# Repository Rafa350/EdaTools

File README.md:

# EdaTools

Tools and utilities for PCB design.
!!!Very early version. Runs ok for my works.

## EdaImport
* Convert EAGLE v7 BRD file to EdaTools board file (.XBRD)
* Convert EAGLE v7 LBR file to EdaTools library file (.XLIB)
* Convert KiCad pcb file to EdaTools board file (.XBRD)

## EdaExport
* Convert EdaTools board file (.XBRD) to EAGLE or KiCAD
* Convert EdaTools library file (.XLIB) to KiCAD footprint library

## EdaExtractor.
* Extract information from board (BOM, Centroids, etc)

## EdaPanelizer.
* Merge any number of boards to create a single board panel.

## EdaCAMTool.
* Create production files from CAM project file (.XCAM).
* Generate gerber X3 image files.
* Generate gerber X3 drill and route files.
* Generate IPC-D356 file.
* Generate IPC-2581C file.
* Compliant with Ucamco Gerber File Format Specification (www.ucamco.com).
* Passed Gerber test with "https://gerber-viewer.ucamco.com/".
* Passed IPC2581C test with 3D PCBA Viewer.

## Notes.
* I used this tool for convert KiCAD to IPC2581 for board fabrication. Pending for assembly.

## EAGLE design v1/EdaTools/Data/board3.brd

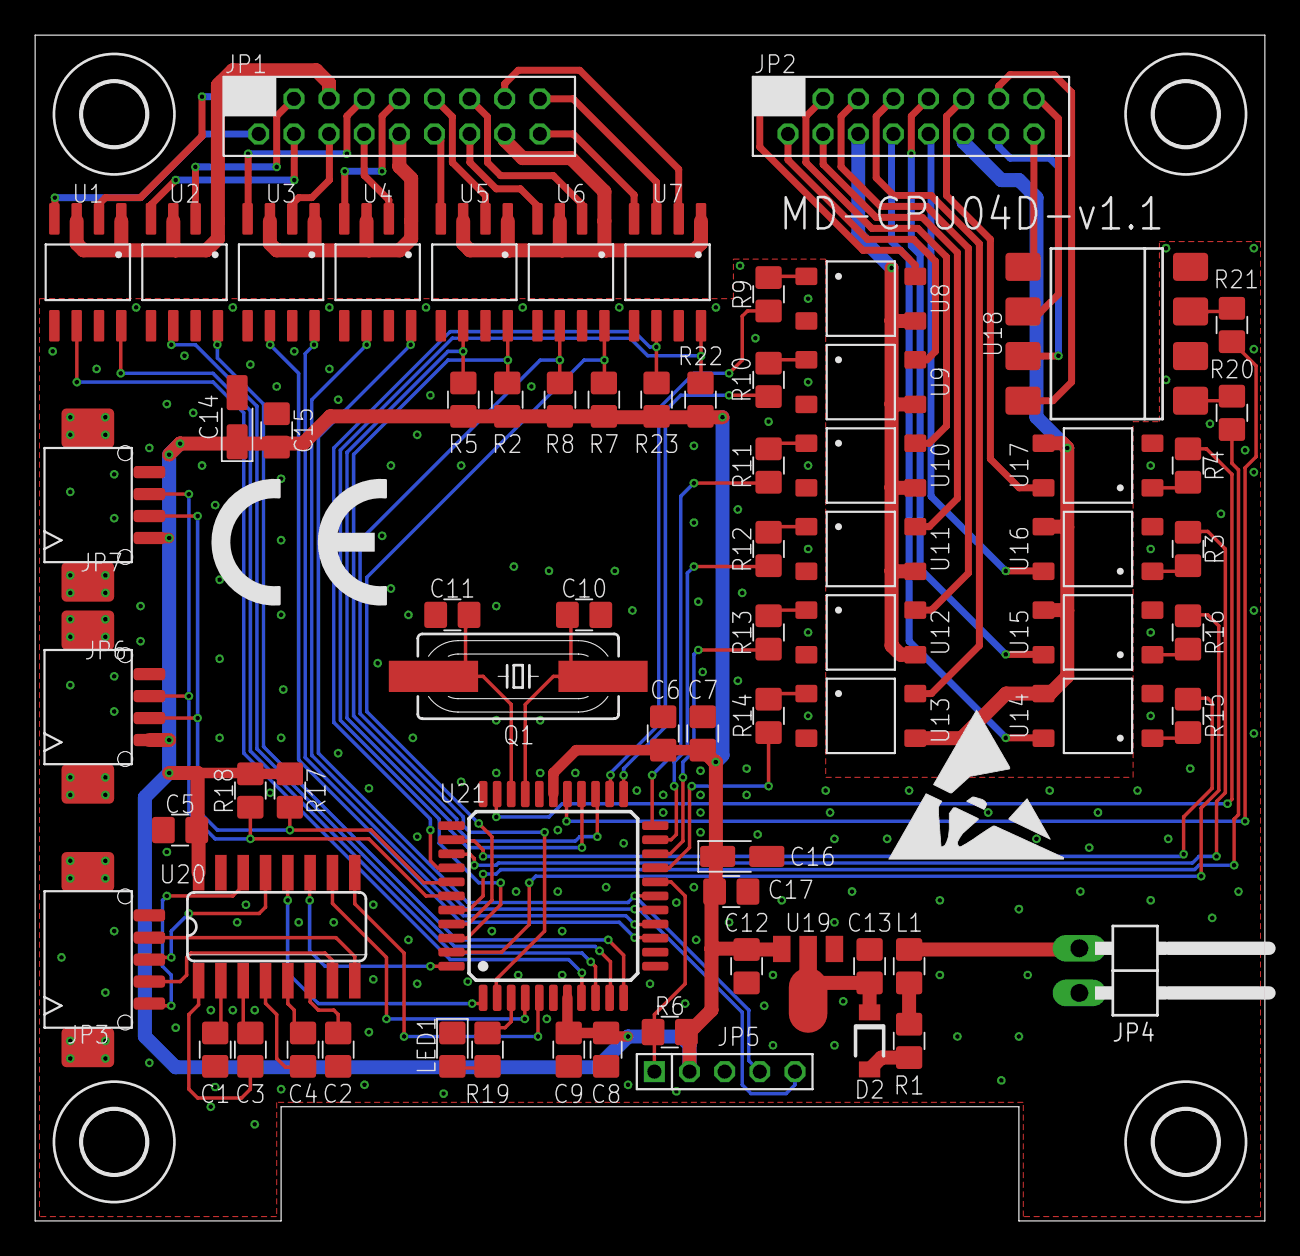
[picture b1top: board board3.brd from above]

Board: 2 copper layers, 70.0 x 67.5 mm, 78 parts (0 on the bottom side), 99 nets.

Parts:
C1, C2, C3, C4, C5, C7, C9, C15, C17: 100n; C-0805
C6, C8: 10n; C-0805
C10, C11: 22p; C-0805
C12, C13: 4u7; C-0805
C14, C16: 10u; C-SMC-A
D2: MBR0540; SOD123FL
JP1: DF11-18DP-2DSA
JP2: DF11-16DP-2DSA
JP3: DF13-1X5-SMD-90-E; 1X5-SMD-90-E
JP4: 1X02/90
JP5: ICSP; 1X05-2MM
JP6, JP7: DF13-1X4-SMD-90-E; 1X4-SMD-90-E
L1: 600R; L-0805
LED1: GREEN; D-LED-0805
Q1: 16MHz; SM49
R1: 5R1; R-0805
R2, R5, R6, R7, R8, R22, R23: 10K; R-0805
R3, R4, R9, R10, R11, R12, R13, R14, R15, R16, R19, R20, R21: 270; R-0805
R17, R18: 1K5; R-0805
U1, U2, U3, U4, U5, U6, U7: ACPL224; SO08
U8, U9, U10, U11, U12, U13, U14, U15, U16, U17: VO1400; SOP04
U18: LH1522AAC; DIL8-SMD
U19: MCP1703T-3302E/MB; SOT89
U20: MAX3232CSE; SO16
U21: PIC18F46K22-I/PT; TQFP44
U$1: CE_7.3MM
U$2: ESD_10.00
U$3, U$6, U$9, U$10: 3,6

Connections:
GND: C1.2, C2.2, C5.1, C6.1, C7.1, C8.1, C9.1, C10.1, C11.1, C12.2, C13.2, C14.2, C15.1, C16.2, C17.1, JP3.5, JP4.2, JP5.3, JP6.4, JP7.4, LED1.C, U1.5, U1.7, U2.5, U2.7, U3.5, U3.7, U4.5, U4.7, U5.5, U5.7, U6.5, U6.7, U7.5, U7.7, U8.2, U9.2, U10.2, U11.2, U12.2, U13.2, U14.2, U15.2, U16.2, U17.2, U18.2, U18.4, U19.1, U20.15, U21.6, U21.29
I0: JP1.1, U1.2
I1: JP1.2, U1.4
I2: JP1.3, U2.2
I3: JP1.4, U2.4
I4: JP1.6, U3.2
I5: JP1.7, U3.4
I6: JP1.8, U4.2
I7: JP1.9, U4.4
I8: JP1.11, U5.2
I9: JP1.12, U5.4
I10: JP1.13, U6.2
I11: JP1.14, U6.4
I12: JP1.15, U7.2
I13A: JP1.17, U7.3
I13B: JP1.18, U7.4
IC0: JP1.5, U1.1, U1.3, U2.1, U2.3
IC1: JP1.10, U3.1, U3.3, U4.1, U4.3
IC2: JP1.16, U5.1, U5.3, U6.1, U6.3, U7.1
IN0: U1.8, U21.9
IN1: U1.6, U21.8
IN2: U2.8, U21.11
IN3: U2.6, U21.10
IN4: U3.8, U21.15
IN5: U3.6, U21.14
IN6/PGD: JP5.4, U4.8, U21.17
IN7/PGC: JP5.5, U4.6, U21.16
IN8: R2.1, U5.8, U21.25
IN9: R5.1, U5.6, U21.26
IN10: R7.1, U6.8, U21.41
IN11: R8.1, U6.6, U21.2
IN12: R22.1, U7.8, U21.42
IN13: R23.1, U7.6, U21.37
LED: R19.2, U21.3
unnamed: R3.2, U16.1
unnamed: JP4.1, L1.2
unnamed: L1.1, R1.1
unnamed: JP3.1, U20.14
unnamed: C13.1, D2.C, U19.2, U19.2@1
unnamed: R4.2, U17.1
unnamed: D2.A, R1.2
unnamed: C10.2, Q1.1, U21.30
unnamed: R20.2, U18.1
unnamed: JP3.2, U20.7
unnamed: JP3.3, U20.13
unnamed: JP3.4, U20.8
unnamed: C3.2, U20.1
unnamed: R9.2, U8.1
unnamed: R10.2, U9.1
unnamed: LED1.A, R19.1
unnamed: R11.2, U10.1
unnamed: R12.2, U11.1
unnamed: C3.1, U20.3
unnamed: C4.2, U20.4
unnamed: C4.1, U20.5
unnamed: C1.1, U20.2
unnamed: C2.1, U20.6
unnamed: C11.2, Q1.2, U21.31
unnamed: R21.2, U18.3
unnamed: R15.2, U14.1
unnamed: R13.2, U12.1
unnamed: R14.2, U13.1
unnamed: R16.2, U15.1
O0: JP2.1, U8.4
O1: JP2.2, U9.4
O2: JP2.3, U10.4
O3: JP2.4, U11.4
O4: JP2.5, U12.4
O5: JP2.7, U13.4
O6: JP2.8, U14.4
O7: JP2.9, U15.4
O8: JP2.10, U16.4
O9: JP2.11, U17.4
O10A: JP2.13, U18.8
O10B: JP2.14, U18.7
O11A: JP2.15, U18.6
O11B: JP2.16, U18.5
OC0: JP2.6, U8.3, U9.3, U10.3, U11.3, U12.3
OC1: JP2.12, U13.3, U14.3, U15.3, U16.3, U17.3
OUT0: R9.1, U21.24
OUT1: R10.1, U21.23
OUT2: R11.1, U21.22
OUT3: R12.1, U21.21
OUT4: R13.1, U21.20
OUT5: R14.1, U21.19
OUT6: R15.1, U21.35
OUT7: R16.1, U21.43
OUT8: R3.1, U21.36
OUT9: R4.1, U21.32
OUT10: R20.1, U21.40
OUT11: R21.1, U21.27
RX1: U20.12, U21.1
RX2: U20.9, U21.5
SCL2: JP6.2, JP7.2, R17.1, U21.38
SDA2: JP6.3, JP7.3, R18.1, U21.39
TX1: U20.11, U21.44
TX2: U20.10, U21.4
VCC: C5.2, C6.2, C7.2, C8.2, C9.2, C12.1, C14.1, C15.2, C16.1, C17.2, JP5.2, JP6.1, JP7.1, R2.2, R5.2, R6.2, R7.2, R8.2, R17.2, R18.2, R22.2, R23.2, U19.3, U20.16, U21.7, U21.28
VPP: JP5.1, R6.1, U21.18

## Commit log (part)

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2018-01-26 Dibuix correcte de poligons en pantalla. Dibuix correcta de rectangles i cercles plens o perfilats Proves amb fons Hershey
2018-01-27 Millores en el gerber per acostar-se al maxim a les especificacions de ucamco Afeigit el parametre BoardSide en la generacio dels poligons
2018-01-27 Renombrada la llibraria CAM Eina CAM per la generacio de gerbers
2018-01-29 Millores en la lectura i escriptura de la placa en un stream
2018-01-29 Commit final del dia
2018-01-31 Afeigit attributs en el bloc Lectura dles atributs al carregar la placa. Eliminada la propietat isolation en les regions. Optimitzacio del generador gerber.
2018-01-31 Revisio dels visitadors Optimitzacio de la generacio dels fitxers gerbers
2018-02-01 Afeigits el readme i la llivcencia per github
2018-02-02 Millores en la deteccio d'errors de parametres en el generador gerber. Modificat la funcio d'escriure atributs gerber. Canvis en noms incongruents.
2018-02-03 Millores en el generador de visuals. Un visual per capa. Cada visual de capa te visuals fills dels elements de la capa. D'aquesta manera es pot controlar la transparencia, el color i la visibilitat d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
2018-02-04 Clase Angle per representar tots els angles de rotacio, arcs, etc El gerber ya representa correctament la separacio del perfil en els poligons
2018-02-06 Modificacions en el visor de plaques
2018-02-07 Implementacio dels fonts heshey Afeigit clearance en les senyals
2018-02-08 Creacio del font standard
2018-02-19 Gestio de fonst vectorials
2018-02-20 Fonts vectorials
2018-02-21 Creacio de fonts. El element text te en compte la rotacio i posicio de l'atribut
2018-02-22 Mes fonts Ajust de l'orientacio dels texts, tant literals, com asignats a un atribut.
2018-02-26 Optimitzacio llistes de poligons
2018-02-27 Reorganitzacio del projecte EdaImport
2018-02-27 Aliniacio textes
2018-02-28 Atributs de Part. Posicio rotacio i aliniacio. Nova clase TextDrawer per dibuixar textes. Es por derivar per dibuixar en qualsevol dispositiu vectorial
2018-03-02 Gestio dels parasmetres dels parts
2018-03-04 Poligons i fonts implementats amb arrays. PolygonBuilder adaptat a arrays de punts. Restructuracio de la carpeta Geometry.
2018-03-06 Creacio de les clases PointInt, SizeInt, i RectInt GlyphPoint es substutuit per PointInt
2018-03-07 Canvi de geometria double a int
2018-03-09 Canvi a aritmetica amb enters
2018-03-10 Complert el traspas a geometria amb enters
2018-03-11 final del dia
2018-03-14 Nou: Generacio de fitxers IPCD365
2018-03-14 Correccio de bugs en el calcul de la corona en vias i pads Millores el la generacio IPCD365
2018-03-15 Nova clase SignalVisitor
2018-03-17 Corregit errors amb arcs de mes de 180 graus
2018-03-21 Fitxers XSL per conversio a fitxers de produccio
2018-03-22 Reorganitzacio del projecte. Nova llibreria EdaCommonLibrary
2018-03-26 Commit de seguretat
2018-04-08 Fix: Peta quant intenta visualitzar una capa inexistent
2018-04-15 Carrega els fonts de la carpeta relativa al executable. Batch de generacio dels fitxers de produccio. Ignora les carpetes els fitxers de produccio (Data/Production/*)
2018-07-20 Millores en la deteccio d'error del importador eagle
2018-07-24 Implementacio GetOutline per l'element regio.
2018-07-25 Millores en la generacio de gerber Correccio en el el generador xsl del bom per eurocircuits
2018-07-26 Arreglos en CircleElement, RectangleElement Reorganitzacio de XmlNodeHelper
2018-07-30 Opcio Filled en objectes rectangle, circle i RegionElement Visuals per cada tipus d'objecte Pbjecte cachePen i cacheBrush com entitats separades
2018-07-30 Visuals de cada element
2018-07-31 Restructuracio del visor de plaques Zoom i pan correctes
2018-07-31 Millores generals en EdaPCBViewer Calcul del tamany de la placa. Bounding box de les linies. Metodes utils en PointInt, SizeInt i RectInt
2018-08-02 Arreglos cosmetics
2018-08-02 Optimitzacio zoom i pan en EdaPCBViewer
2018-08-06 Gnenerador CAM per fitxers DXS del perfil de la placa
2018-08-07 VisualDrawer optimitzat e independitzat de la resta.
2018-08-10 Nou lector de plaques. Gestio dels pads en els blocs millorada. Creacio retardade de les llistes d'atributs i pads
2018-08-12 Restructuracio Geometry Millores en la importacio Eagle Optimitzacio en XmlBoardReader i XmlBoardWriter Arreglos cosmetics generals
2018-08-13 Restructuracio dels fitxers i carpetes. Clases XmlWriterAdapter i XmlReaderAdapter. Cleses helper per Xml en cada tipus que ho necesiti. Mes lletres en els fonmts Nova clase DistanceUnits Nova clase 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
2018-08-27 Generacio de fitxers CAM per panells multiplaca
2018-08-28 Restructuracio del model
2018-08-29 Panelitzacio en la sortida gerber Lecturs de panells XPNL
2018-08-30 Generador CAM per ipc-d356 per panell
2018-09-07 Restructuracio de la gestio de capes. Cada element de la placa te el seu LayerSet on constant en quines capes el renderitzen. Si la placa en la que esta te una capa del LayerSet, la dibuixa, si no, c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
2018-09-07 Restructuracio general. Funcio Clone en elements de placa. Funcions d'extensio en XmlReaderAdapter pels tipus basics (Point, Size, Angle, etc
2018-09-08 Millores en el panelitzador. Gestio de les capes amb LayerId, i LayerSet Gestio de la capa outlineLayer
2018-09-09 Millores en el panelitzador. Revisio Block canvi de HashSet per List
2018-09-10 Implementacio amb noves col·leccions
2018-09-10 Proves amb WriteableBitmap
2018-09-11 Restructuracio dels fitxers board
2018-09-11 Millores en les coleccions per evitar memory leaks
2018-09-12 Revisio coleccions
2018-09-15 Restructuracio del render WPF
2018-09-16 Caper visuals (En estudi)
2018-09-19 Restructuracio en lectura i escriptura de fitxers XBRD
2018-09-20 Restructuracio
2018-09-27 Optimitzacione en el renderitzat
2018-10-20 Cambis cosmetics
2018-11-01 Millores en la carrega del projecte XCAM
2018-11-02 Millores en el generador CAM
2018-11-06 Millores en el procesador CAM
2018-11-16 Millores en la lectura dels fitxers de placa
2018-11-16 Corregit: No troba el schema per la lectura del fitxer XPNL
2018-11-19 Millores en la lectura de fitxers XPNL, XBRD i XCAM Hole nomes en la capa Hole, implicitament afecta a totes. Lectura de posicio i rotacio en projectes CAM
2018-11-21 Canvis en el format del fitxer xpnl
2018-11-23 Nou projecte EdaHDCLibrary
2018-11-25 Compilador HDL
2018-11-27 Millores en el parser HDL
2018-11-28 Gramatica pel HDL
2018-11-29 Parser PHDL completat Objectes AST complert
2018-11-29 Afeigit TODO
2018-11-30 Restructuracio de EdaPCBLibrary
2018-12-01 Restructuracio del model. Simplicifacio de les coleccions.
2018-12-02 Restructuracio i simplificacio
2018-12-04 Millores en el panelitzador
2018-12-04 Panelitzador
2018-12-06 Millores en el panelitzador.
2018-12-08 Correccio error greu en LayerSet.Parse que impedia la identificacio corerecte de les capes Correccio en la posicio del forats en els fitxers gerber
2018-12-09 Millores en el parser de LayerId
2018-12-10 Restructuracio en la llibraria EdaCAM
2018-12-11 Parametres d'entrada al panelitzador. Millores en el build
2018-12-13 Restructuracio i millores en l'editor de panells
2018-12-15 Restructuracio dels visitadors
2018-12-17 Restructuracio de BoardEditor Objectes visuals per BoardEditor
2018-12-21 Restructuracio dels editors Nou ensamblat per grafics wpf
2018-12-21 Mapa de conectivitat inici de la implementacio
2018-12-22 Restructuracio del editor de panells Simplificacio del renderitzat
2018-12-31 Canvi del format dels fitxert xpnl Correccio d'errors en el panelitzador i en el editor de panells
2018-12-31 Actualitzacio projecte doxygen
2019-01-05 Correccio del renderitzat de poligons en parts situats en la capa inferior
2019-01-07 Millores en VisualLayer
2019-01-09 Millores en EdaPanelizer Correccio d'errors en Setup
2019-01-09 Canvi en la forma d'identificar si un part esta voltejat Objecte IStreamLocator, per localitzar streams en els projectes
2019-01-11 Remodelacio de les capes Importar Eagle
2019-01-13 Restructuracio EdaCAMTool
2019-01-17 Restructuracio EdaPanelizer y EdaCamTool
2019-01-18 Perfil de les plaques en el editor de panells
2019-01-23 Canvis en la llista d'ignorats
2019-01-24 Millores en EdaPanelizer i en EdaPanelEditor
2019-01-26 Elimina la clase Color per innecesaria
2019-02-01 Correccions en el panelitzador Millores en la visualitzacio del editor de panells
2019-02-02 Afeigida la gestio de llibreries de components
2019-02-04 Mes lletres en el font per defecte Correccio d'errors en el visual dels textos
2019-02-05 Proves amb netlist
2019-02-07 Correccions al importar el netlist desde eagle
2019-02-08 Canvis en el sistema de renderitzat en PanelEditor
2019-02-10 Restructuracio en DesignTool
2019-02-12 Eliminacio de Angle en DesignTool
2019-02-16 Correccions en EdaPanelEditor
2019-02-18 Canvis cosmetics
2019-02-19 Restructuracio i millores en RulerBox
2019-02-22 Millores en ContentBox
2019-02-28 Canvis en les eines de dibuix.
2019-03-30 Verificacio de capes duplicades en AddLayer
2019-04-07 Millores al importar Eagle Preparacio por importar KiCad
2019-04-27 Canvis en els ViewModel
2019-06-19 Canvis en Rect i en Size
2019-08-27 Optimitzacio i millores en WindowState
2019-12-31 Restructuracio general per identificar versions
2020-01-03 Afeigit carpeta d'exemles i proves
2020-01-04 Canvi a nova versio v2.0. -NET Core v3.1
2020-01-04 Correccions en les propietats dels paquets.
2020-01-10 Millores en matrius 2D. Obtingut de AvaloniaUI
2020-01-10 interface Equatable<> en Point, Angle, etc. Nova clase Corners.
2020-01-12 Control RulerBox
2020-01-14 Millores en la regla
2020-02-24 Milleres en el controls de diseny
2020-02-25 Millores en renderitzar dels controls de diseny
2020-03-04 Intent de crear un editor grafic generic Nou SceneControl per mostrasr escenes.
2020-03-08 Cache de poligons. Llista de punts inmutable. Eines de dibuix. Restructuracio SceneView.
2020-05-20 Canvis en la llicencia
2020-05-28 Restructuracio carpetes
2020-06-27 Millores en el importador Kicad
2020-06-28 Millores importacio KiCad
2020-07-02 Revisions cosmetiques
2021-05-03 Importacio i exportacio Kicad
2021-05-04 Importacio kicad
2021-05-08 Correccions en l'aliniacio de textos. Correccions en la substitucio de macros {} Correccions en la importacio KiCad
2021-05-08 Compressio de la versio antiga
2021-05-11 bug: IPCD356 vies sense senyal asignada provocan excepcio: resolt
2021-05-12 Nova aplicacio EdaCOmpònentGenerator
2021-05-19 Correccio bug en el renderitzat dels poligons. Revisio en la importacio KiCad
2021-05-22 Rediseny de capes i identificador de capes
2021-05-28 Extensio per la clase Component Unificacio esquemes XBRD i XLIB Revisio Doxygen
2021-06-07 Revisio IVisitable Actualitzacio Avalonia
2021-12-14 Generacio del fitxer Gerber-JOB
2021-12-15 Millorres en gerber-job
2021-12-19 Revisio ThPad i SmdPad clase EdaPoints
2021-12-24 Revisio EagleImport
2021-12-27 Importar KiCad 6
2022-01-17 Importa propietats de la placa Kicad
2022-01-23 Millores en Gerber drill/route Eliminacio del element Hole
2022-02-06 Millores en la compatibilitat KiCad 6
2022-02-07 Millores en la generacio gerber Millores en la importacio KiCad i Eagle Pads i slots
2022-02-13 Millora importacio arcs KiCad
2022-06-15 Revisio d'errors en la exportacio a KiCad 6
2022-10-09 Revisio generasls dels poligons. Canvi a versio 2 de clipper.
2022-10-12 Revisio regions, thermals, etc
2022-10-12 Filled en Circle, Rectangle i Polygon
2022-10-13 Revisio poligons
2022-10-14 Resisio importador KiCad
2022-10-16 Utilitza alia pels noms de senyals en el fitxer IPC-356-A
2022-10-17 Nova llibraria EddaCoreExtensions Millores en la exportacio IPC2581
2022-10-19 Revisio IPC2581Generator
2022-10-20 Revisio IPC2581
2022-10-23 Comit
2022-10-24 Revisio IPC2581, versio preliminar utilitzable
2022-10-24 Asignacio de nom segur a tots els projectes
2022-10-26 Revisio de la gestio del senyals
2022-10-30 Afeigit silkscreen en el fitxer IPC2582
2022-10-31 Cache de poligons per m,illorar la velocitat de renderitzat. Redistribucio dels espai de noms IO
2022-11-01 Revisio cercles en LayerFeatures en IPC-2581 Importacio de cercvles en Kicad Revisio EdaBoardViewer
2022-11-02 EdaLineBaseElement com a base abstracta per linies i arcs
2022-11-19 Correccio offsets amb Clipper2
2022-12-17 Revisio IPC2581 Tots els angles (EdaAngle) son sempre normalitzats.
2022-12-18 Revisio errors en la importacio del plaques KiCad
